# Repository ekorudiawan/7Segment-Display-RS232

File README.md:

# 7Segment-Display-RS232
7Segment Display RS232

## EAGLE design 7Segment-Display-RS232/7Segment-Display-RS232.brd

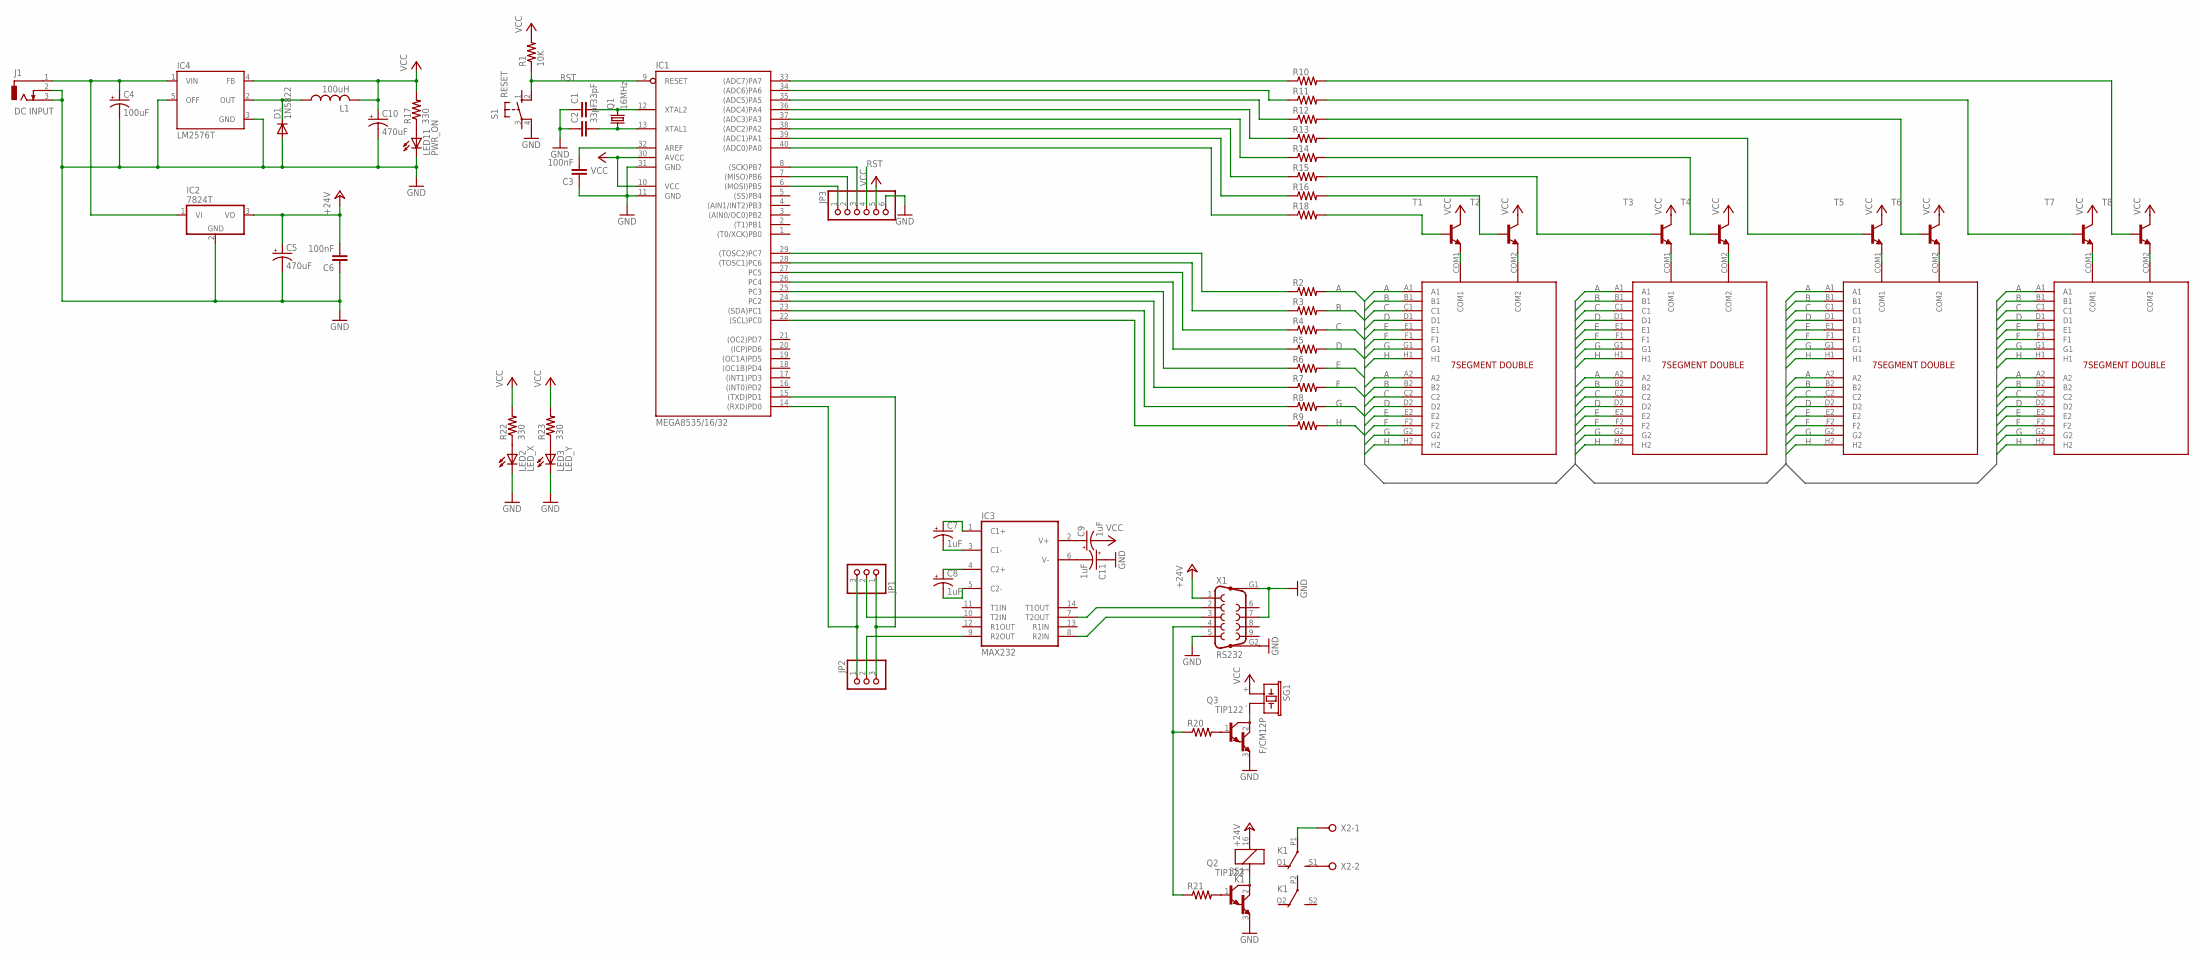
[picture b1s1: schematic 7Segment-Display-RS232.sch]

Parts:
C1, C2: 33pF; C025-024X044
C3, C6: 100nF; C025-024X044
C4: 100uF; E2,5-6
C5, C10: 470uF; E3,5-8
C7, C8, C9, C11: 1uF; E2-4
D1: 1N5822; DO201-15
IC1: MEGA8535/16/32; DIL40
IC2: 7824T; TO220H
IC3: MAX232; DIL16
IC4: LM2576T; TO220-5
J1: DC INPUT; DCJ0202
JP1, JP2: PINHD-1X3; 1X03
JP3: PINHD-1X6; 1X06
K1: 351
L1: 100uH; TJ3-U2
LED2: LED_X; LED3MM
LED3: LED_Y; LED3MM
LED11: PWR_ON; LED3MM
Q1: 16MHz; HC49/S
Q2, Q3: TIP122; TO220
R1: 10K; 0207/10
R2, R3, R4, R5, R6, R7, R8, R9, R10, R11, R12, R13, R14, R15, R16, R18, R20, R21: R-US_0207/2V; 0207/2V
R17, R22, R23: 330; 0207/2V
S1: RESET; B3F-10XX
SG1: F/CM12P
T1, T2, T3, T4, T5, T6, T7, T8: 2N2222-NPN-TO92-EBC; TO92-EBC
U$1, U$2, U$3, U$4: 7SEGMENT_DOUBLE
X1: RS232; F09HP
X2: W237-02P; W237-132

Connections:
+24V: C5.+, C6.2, IC2.3 (VO), K1.16 (2), X1.1
A: R2.2, U$1.A1, U$1.A2, U$2.A1, U$2.A2, U$3.A1, U$3.A2, U$4.A1, U$4.A2
B: R3.2, U$1.B1, U$1.B2, U$2.B1, U$2.B2, U$3.B1, U$3.B2, U$4.B1, U$4.B2
C: R4.2, U$1.C1, U$1.C2, U$2.C1, U$2.C2, U$3.C1, U$3.C2, U$4.C1, U$4.C2
D: R5.2, U$1.D1, U$1.D2, U$2.D1, U$2.D2, U$3.D1, U$3.D2, U$4.D1, U$4.D2
E: R6.2, U$1.E1, U$1.E2, U$2.E1, U$2.E2, U$3.E1, U$3.E2, U$4.E1, U$4.E2
F: R7.2, U$1.F1, U$1.F2, U$2.F1, U$2.F2, U$3.F1, U$3.F2, U$4.F1, U$4.F2
G: R8.2, U$1.G1, U$1.G2, U$2.G1, U$2.G2, U$3.G1, U$3.G2, U$4.G1, U$4.G2
GND: C1.1, C2.1, C3.1, C4.-, C5.-, C6.1, C10.-, C11.+, D1.A, IC1.11 (GND), IC1.31 (GND), IC2.2 (GND), IC3.15 (GND), IC4.3 (GND), IC4.5 (OFF), J1.2, J1.3, JP3.6, LED2.K (C), LED3.K (C), LED11.K (C), Q2.3 (E), Q3.3 (E), S1.4 (P1), X1.5, X1.7, X1.G1, X1.G2
H: R9.2, U$1.H1, U$1.H2, U$2.H1, U$2.H2, U$3.H1, U$3.H2, U$4.H1, U$4.H2
unnamed: T8.E, U$4.COM2
unnamed: T7.E, U$4.COM1
unnamed: C1.2, IC1.12 (XTAL2), Q1.2
unnamed: T1.E, U$1.COM1
unnamed: T2.E, U$1.COM2
unnamed: T3.E, U$2.COM1
unnamed: T4.E, U$2.COM2
unnamed: T5.E, U$3.COM1
unnamed: T6.E, U$3.COM2
unnamed: C2.2, IC1.13 (XTAL1), Q1.1
unnamed: C3.2, IC1.32 (AREF)
unnamed: C4.+, IC2.1 (VI), IC4.1 (VIN), J1.1
unnamed: R18.2, T1.B
unnamed: R16.2, T2.B
unnamed: R15.2, T3.B
unnamed: R14.2, T4.B
unnamed: R13.2, T5.B
unnamed: R12.2, T6.B
unnamed: R11.2, T7.B
unnamed: R10.2, T8.B
unnamed: IC1.33 ((ADC7)PA7), R10.1
unnamed: IC1.34 ((ADC6)PA6), R11.1
unnamed: IC1.35 ((ADC5)PA5), R12.1
unnamed: IC1.36 ((ADC4)PA4), R13.1
unnamed: IC1.37 ((ADC3)PA3), R14.1
unnamed: IC1.38 ((ADC2)PA2), R15.1
unnamed: IC1.39 ((ADC1)PA1), R16.1
unnamed: IC1.40 ((ADC0)PA0), R18.1
unnamed: IC1.29 ((TOSC2)PC7), R2.1
unnamed: IC1.28 ((TOSC1)PC6), R3.1
unnamed: IC1.27 (PC5), R4.1
unnamed: D1.C, IC4.2 (OUT), L1.1
unnamed: LED11.A, R17.1
unnamed: IC1.26 (PC4), R5.1
unnamed: IC1.25 (PC3), R6.1
unnamed: IC1.24 (PC2), R7.1
unnamed: IC1.23 ((SDA)PC1), R8.1
unnamed: IC1.22 ((SCL)PC0), R9.1
unnamed: C7.-, IC3.3 (C1-)
unnamed: Q3.1 (B), R20.2
unnamed: R20.1, R21.1, X1.4
unnamed: Q2.1 (B), R21.2
unnamed: C8.+, IC3.4 (C2+)
unnamed: C7.+, IC3.1 (C1+)
unnamed: C8.-, IC3.5 (C2-)
unnamed: C9.+, IC3.2 (V+)
unnamed: C11.-, IC3.6 (V-)
unnamed: IC3.7 (T2OUT), X1.2
unnamed: IC3.8 (R2IN), X1.3
unnamed: IC1.14 ((RXD)PD0), JP1.3, JP2.1
unnamed: IC1.15 ((TXD)PD1), JP1.1, JP2.3
unnamed: IC3.9 (R2OUT), JP2.2
unnamed: IC3.10 (T2IN), JP1.2
unnamed: LED3.A, R23.1
unnamed: LED2.A, R22.1
unnamed: IC1.6 ((MOSI)PB5), JP3.1
unnamed: IC1.7 ((MISO)PB6), JP3.2
unnamed: IC1.8 ((SCK)PB7), JP3.3
unnamed: Q3.2 (C), SG1.- (2)
unnamed: K1.1, Q2.2 (C)
unnamed: K1.S1 (S), X2.2
unnamed: K1.P1, X2.1
RST: IC1.9 (RESET), JP3.4, R1.1, S1.2 (S1)
VCC: C9.-, C10.+, IC1.10 (VCC), IC1.30 (AVCC), IC3.16 (VCC), IC4.4 (FB), JP3.5, L1.2, R1.2, R17.2, R22.2, R23.2, SG1.+ (1), T1.C, T2.C, T3.C, T4.C, T5.C, T6.C, T7.C, T8.C

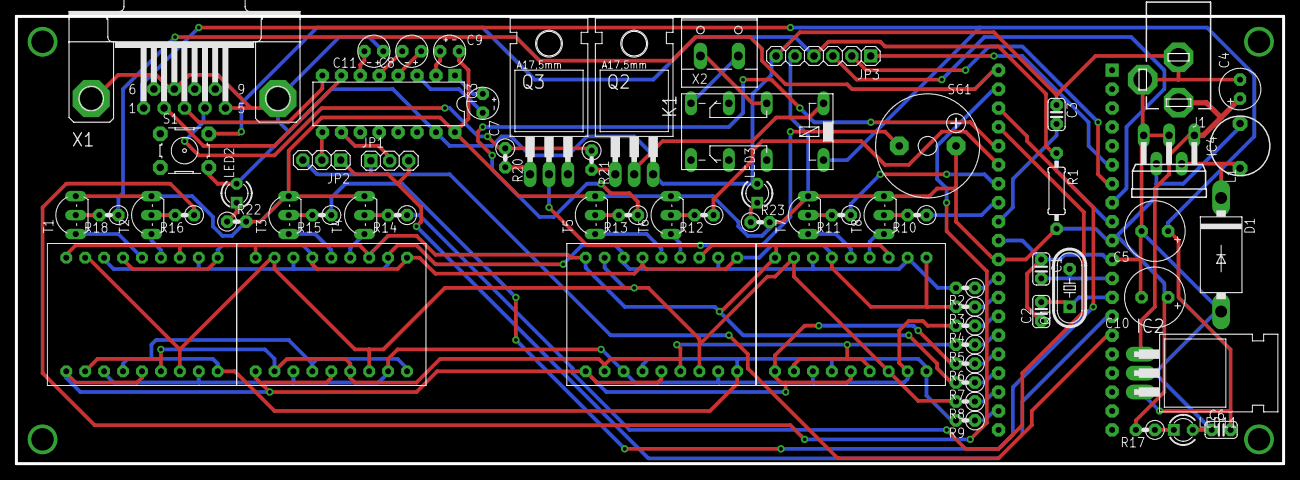
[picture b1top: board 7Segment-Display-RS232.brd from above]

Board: 2 copper layers, 170.0 x 60.0 mm, 66 parts (1 on the bottom side), 74 nets.

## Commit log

2017-10-03 Added HW Design Files
